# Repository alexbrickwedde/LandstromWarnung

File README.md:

# LandstromWarnung

Platine zur Warnung wenn Zündung eingeschaltet wird und noch Landstrom verbunden ist. Muss mit Klemme 15 und Fahrzeug-Masse verbunden werden. Andererseits and + und - von 12V die durch Landstrom zur Verfügung gestellt werden. Die Massen sind nicht verbunden! Der Summer wird vom Landstrom versorgt. Von Klemme 15 wird nur ein Optokoppler angesteuert, Vorwiderstand muss entsprechend dimensioniert werden (v.a. in der Leistung) . Achtung: Kein CE, kein E-Prüfzeichen.

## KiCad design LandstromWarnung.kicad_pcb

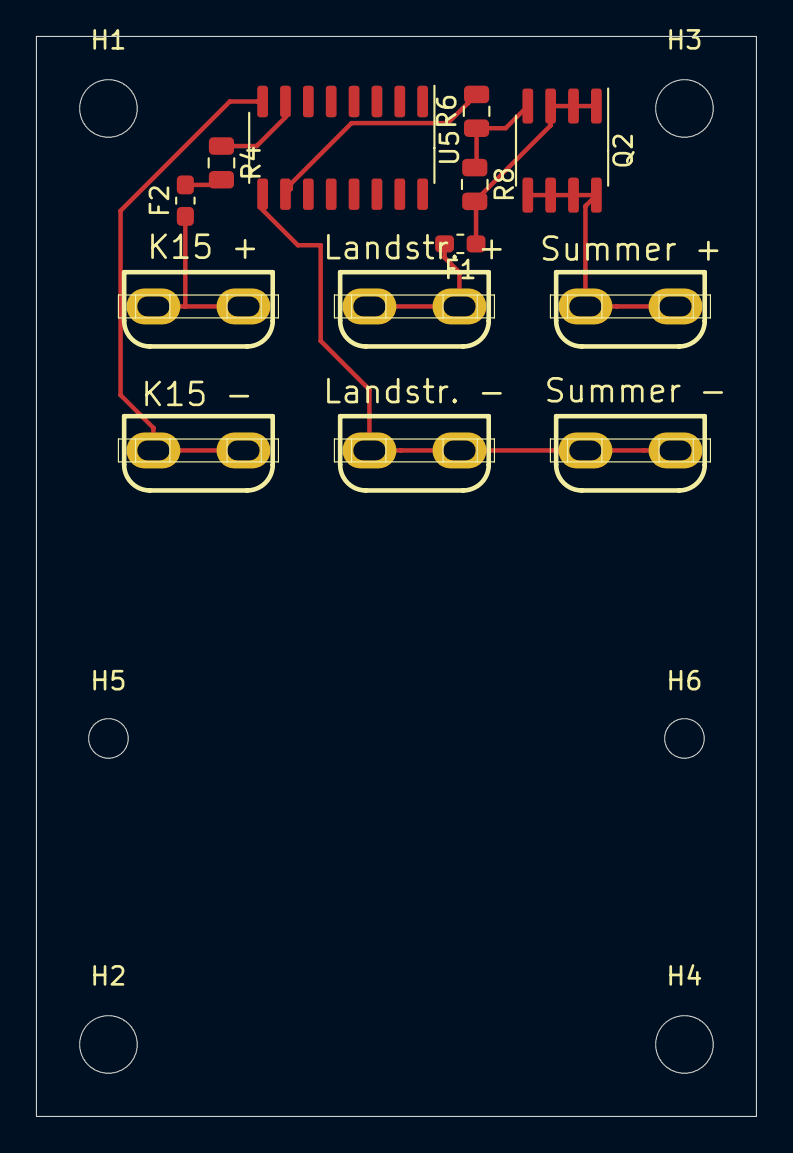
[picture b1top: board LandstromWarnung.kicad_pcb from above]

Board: 4 copper layers, 40.0 x 60.0 mm, 19 parts (0 on the bottom side), 10 nets.

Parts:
F1, F2: Polyfuse; R_0603_1608Metric_Pad1.05x0.95mm_HandSolder
H1, H2, H3, H4: MountingHole; MountingHole_3.2mm_M3_DIN965
H5, H6: MountingHole; MountingHole_2.2mm_M2
J3: Summer -; FASTON-6_3mm
J7: Landstr. +; FASTON-6_3mm
J8: Landstr. -; FASTON-6_3mm
J9: K15 +; FASTON-6_3mm
J10: K15 -; FASTON-6_3mm
J11: Summer +; FASTON-6_3mm
Q2: IRF7404; SOIC-8_3.9x4.9mm_P1.27mm
R4, R6, R8: R; R_0805_2012Metric
U5: LTV-847; SO-16_3.9x9.9mm_P1.27mm

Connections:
+12V: F1.1, Q2.1, Q2.2, Q2.3, R8.2
/K15_minus: J10.1, U5.8
/K15_plus: F2.2, R4.2
/Warn_plus: J11.1, Q2.5, Q2.6, Q2.7, Q2.8
GND: J3.1, J8.1, U5.9
unnamed: F1.2, J7.1
unnamed: F2.1, J9.1
unnamed: Q2.4, R6.1, R8.1
unnamed: R4.1, U5.7
unnamed: R6.2, U5.10

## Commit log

2021-03-01 First
